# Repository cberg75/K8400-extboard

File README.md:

# K8400-extboard
Alternative extension board for Velleman Vertex K8400 3D printer

After a few years of good work of my 3D printer, it failed.
Instead of a quick fix, I decided for an upgrade.
I wanted to mount a double E3DV6 hotend.
For the mechanical parts I took inspiration from this project.
https://www.thingiverse.com/thing:2177331
but I did not liked the original extension board. I was worried about the current load on heat cartridges. 
And wanted a more reliable connection and easier mouting-unmounting options.

So this project design a new board with better connections that fits in a new mechanical design that I will link as soon as it is complete.

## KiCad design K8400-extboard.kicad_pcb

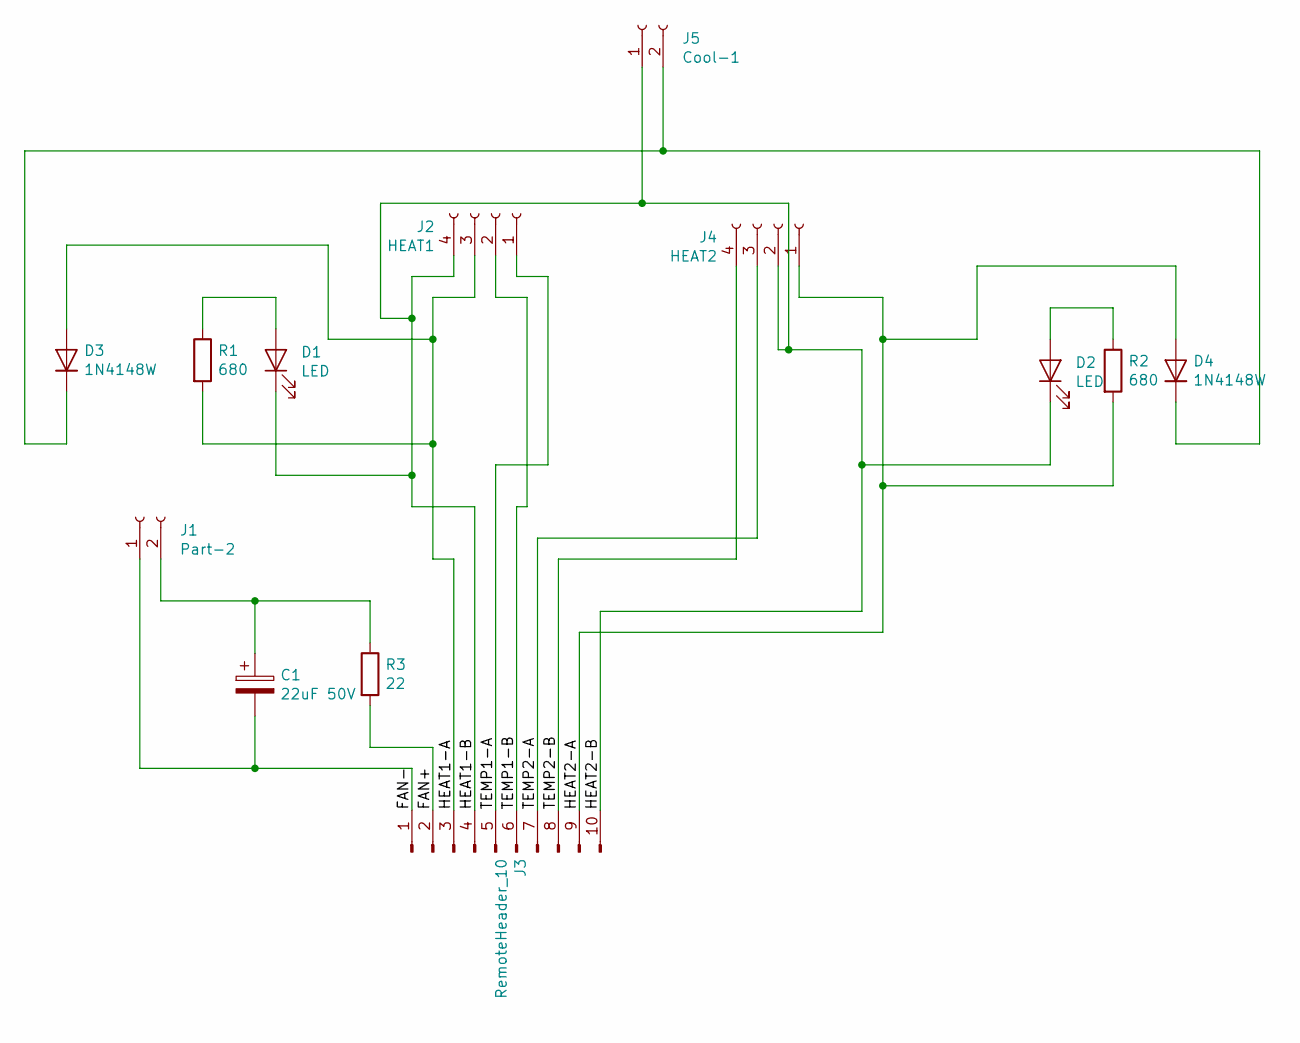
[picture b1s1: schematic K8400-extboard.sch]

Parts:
C1: 22uF 50V; CP_Radial_D5.0mm_P2.50mm
D1, D2: LED; LED_1206_3216Metric
D3, D4: 1N4148W; D_SOD-123
J1: Part-2; Molex_KK-254_AE-6410-02A_1x02_P2.54mm_Vertical
J2: HEAT1; Molex_KK-254_AE-6410-04A_1x04_P2.54mm_Vertical
J3: RemoteHeader_10; Molex_KK-254_AE-6410-10A_1x10_P2.54mm_Vertical
J4: HEAT2; Molex_KK-254_AE-6410-04A_1x04_P2.54mm_Vertical
J5: Cool-1; Molex_KK-254_AE-6410-02A_1x02_P2.54mm_Vertical
R1, R2: 680; R_1206_3216Metric
R3: 22; R_1206_3216Metric

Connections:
/FAN+: J3.2, R3.2
/FAN-: C1.2, J1.1, J3.1
/HEAT1-A: D3.2 (A), J2.3, J3.3, R1.2
/HEAT1-B: D1.1 (K), D2.1 (K), J2.4, J3.4, J3.10, J4.2, J5.1
/HEAT2-A: D4.2 (A), J3.9, J4.1, R2.2
/TEMP1-A: J2.1, J3.5
/TEMP1-B: J2.2, J3.6
/TEMP2-A: J3.7, J4.3
/TEMP2-B: J3.8, J4.4
unnamed: C1.1, J1.2, R3.1
unnamed: D1.2 (A), R1.1
unnamed: D2.2 (A), R2.1
unnamed: D3.1 (K), D4.1 (K), J5.2

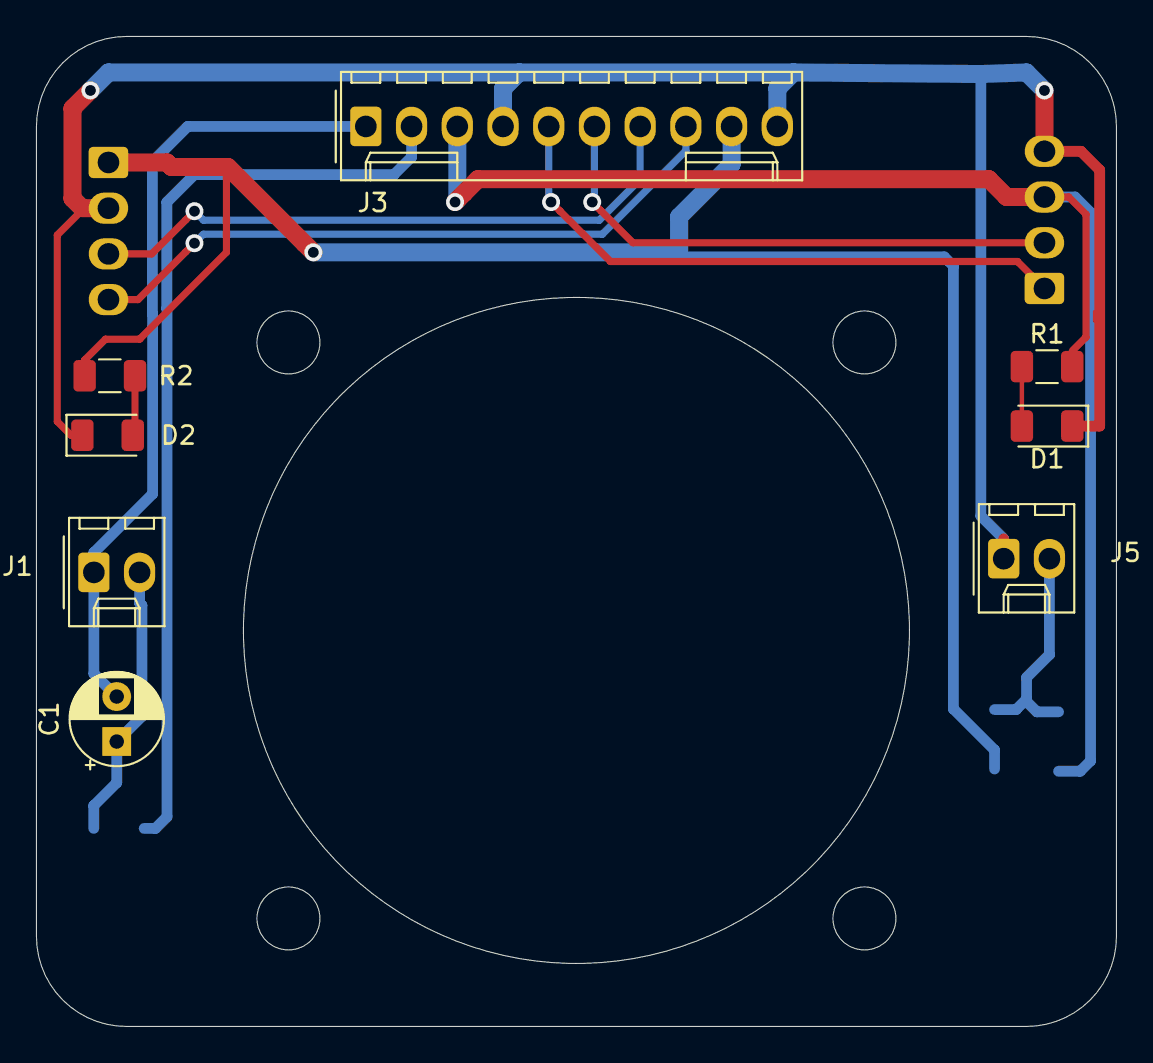
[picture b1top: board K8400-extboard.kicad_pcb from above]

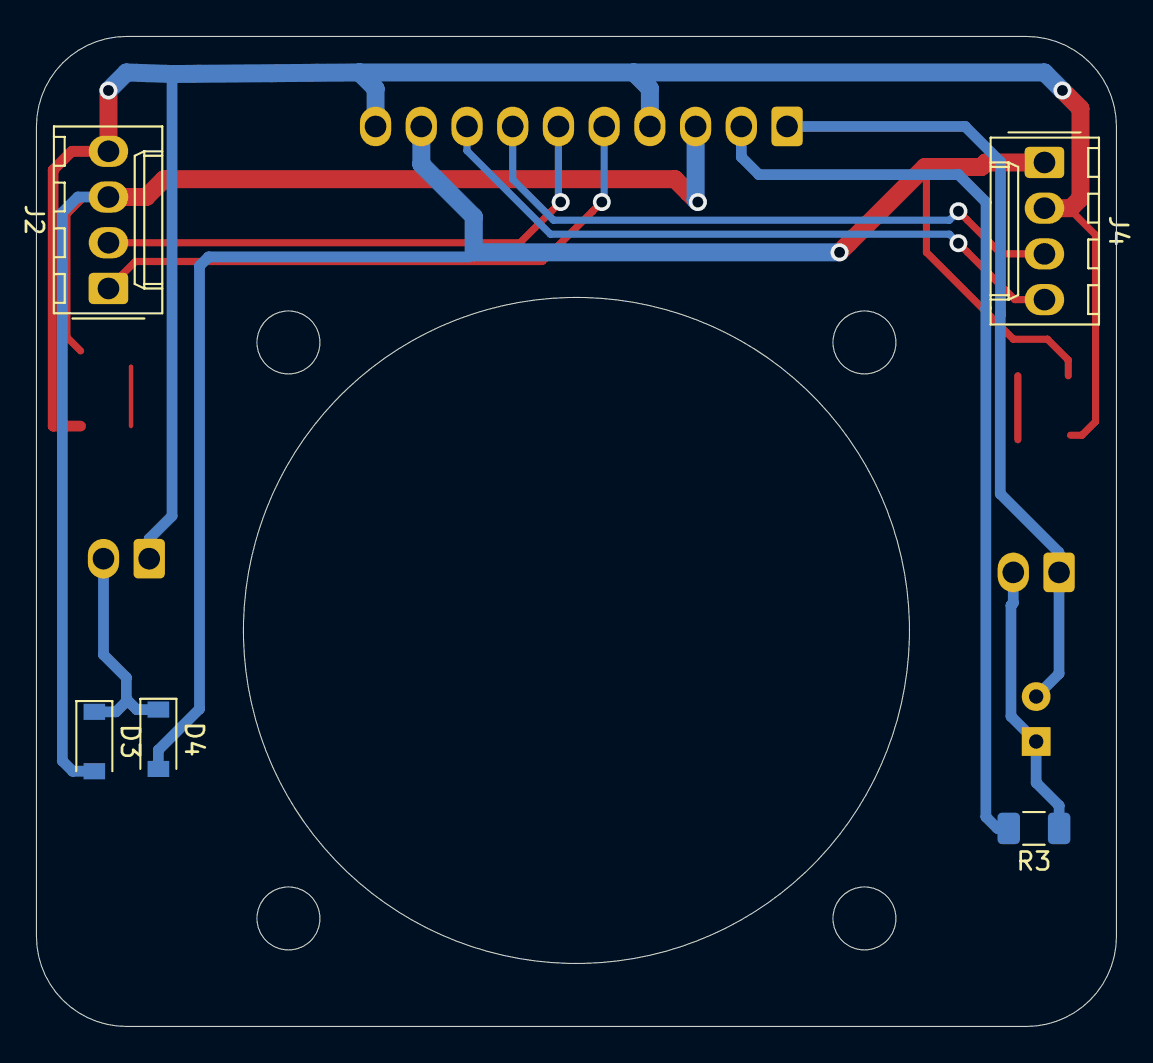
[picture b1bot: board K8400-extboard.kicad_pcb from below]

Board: 2 copper layers, 60.0 x 55.0 mm, 13 parts (5 on the bottom side), 13 nets.

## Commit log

2020-04-17 Initial project version
2020-04-17 Initial project version 2
2020-04-20 Smaller board Polazrized capacitor through the hole smaller LEDs
2020-04-28 Wired
2020-04-28 Track 0.4
